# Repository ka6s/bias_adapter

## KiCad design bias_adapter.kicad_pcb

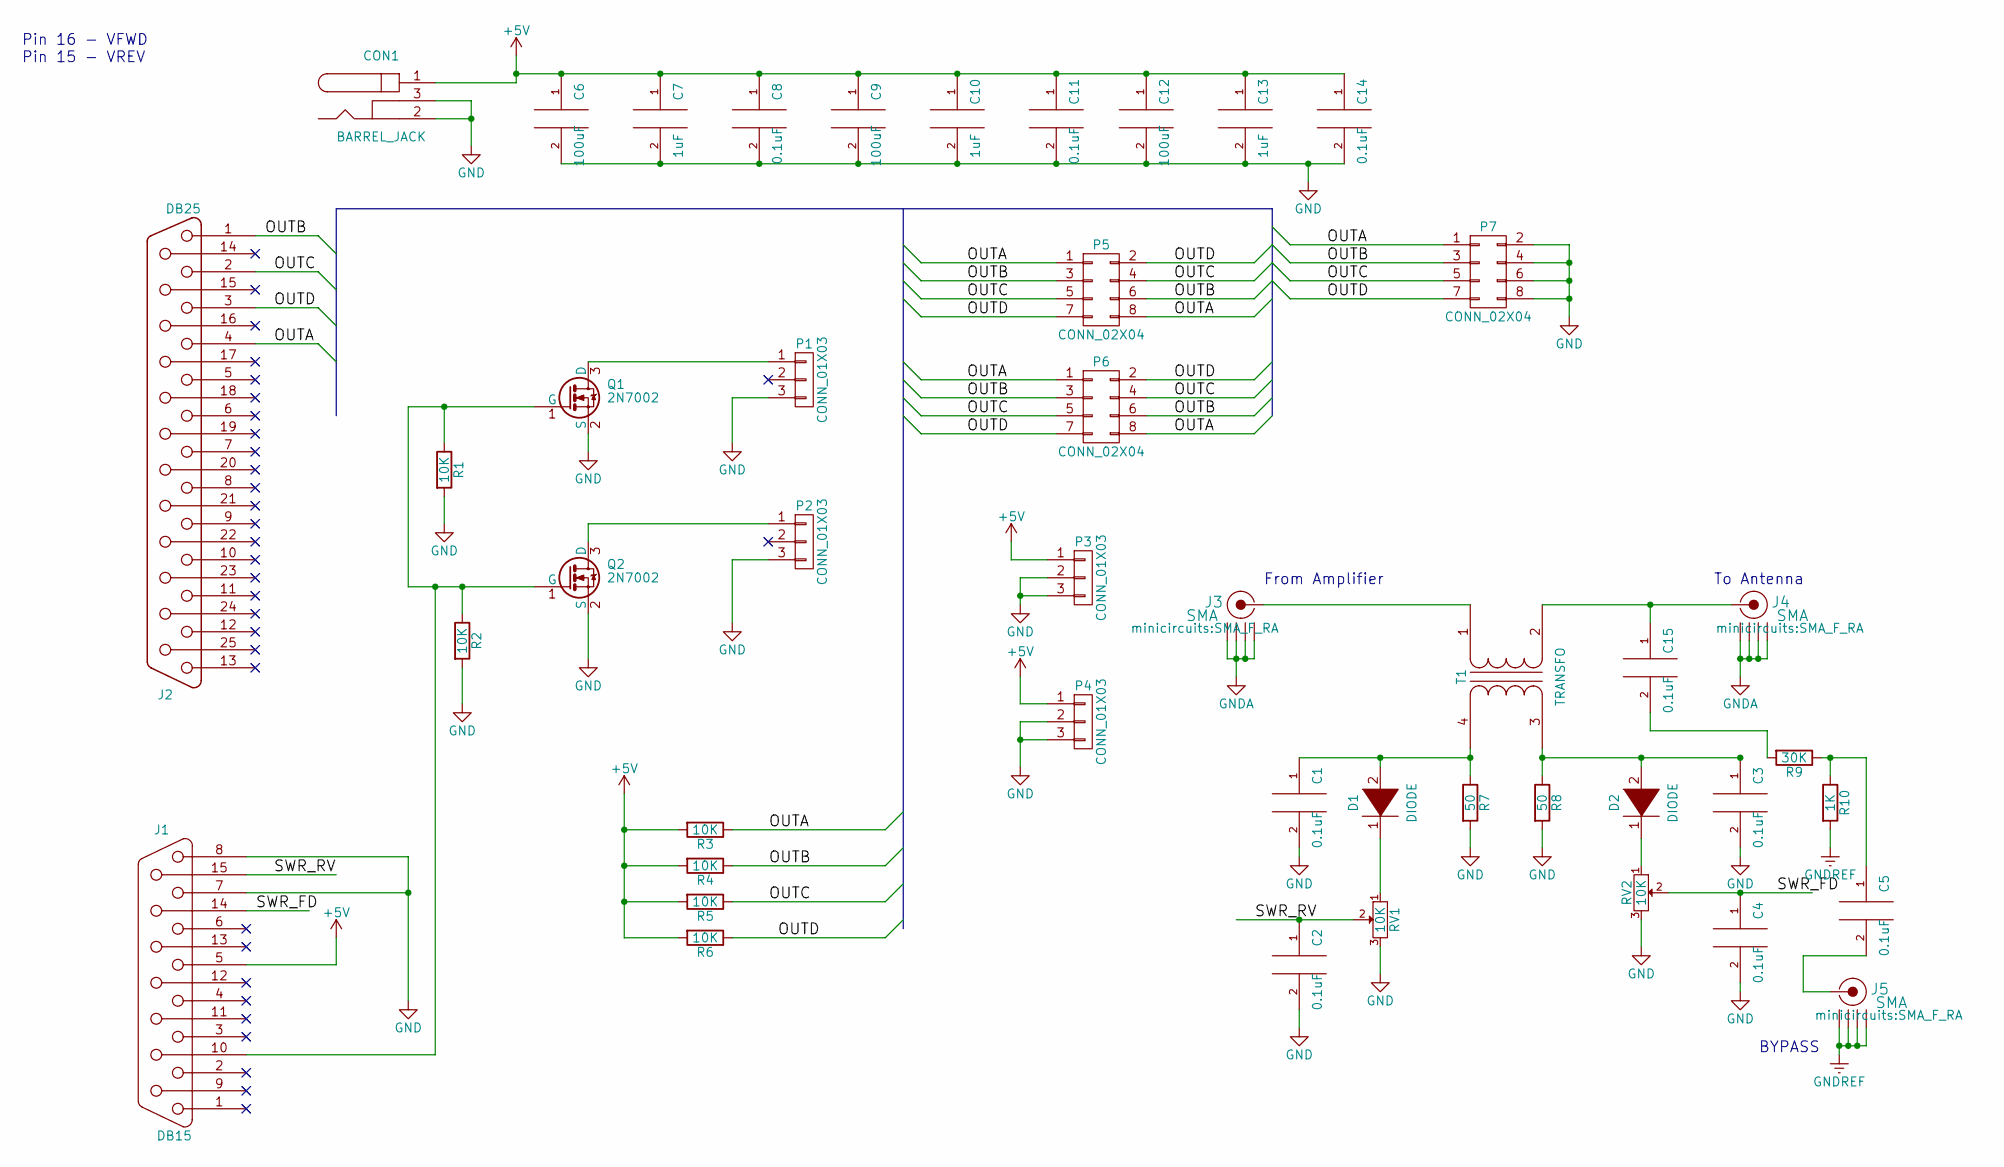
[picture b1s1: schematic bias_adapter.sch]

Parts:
C1, C2, C3, C4, C5, C8, C11, C15: 0.1uF; C_1206_HandSoldering
C6, C9, C12: 100uF; C_1210_HandSoldering
C7, C10, C13: 1uF; C_1210_HandSoldering
C14: 0.1uF; C_1206
CON1: BARREL_JACK
D1, D2: DIODE; Diode_DO-35_SOD27_Horizontal_RM10
J1: DB15; DB15FD
J2: DB25; DB25FD
J3, J4, J5: SMA; SMA_F_RA
P1, P2, P3, P4: CONN_01X03; Pin_Header_Straight_1x03
P5, P6, P7: CONN_02X04; Pin_Header_Straight_2x04
Q1, Q2: 2N7002; SOT-23
R1, R2, R3, R4, R5, R6: 10K; R_1206_HandSoldering
R7, R8: 50; Resistor_Horizontal_RM7mm
R9: 30K; Resistor_Horizontal_RM7mm
R10: 1K; Resistor_Horizontal_RM7mm
RV1, RV2: 10K; Potentiometer_Bourns_3296P_3-8Zoll_Angular_ScrewFront
T1: TRANSFO; NetTie-III

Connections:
+5V: C6.1, C7.1, C8.1, C9.1, C10.1, C11.1, C12.1, C13.1, C14.1, CON1.1, J1.5, P3.1, P4.1, R3.2, R4.2, R5.2, R6.2
/OUTA: J2.4, P5.1, P5.8, P6.1, P6.8, P7.1, R3.1
/OUTB: J2.1, P5.3, P5.6, P6.3, P6.6, P7.3, R4.1
/OUTC: J2.2, P5.4, P5.5, P6.4, P6.5, P7.5, R5.1
/OUTD: J2.3, P5.2, P5.7, P6.2, P6.7, P7.7, R6.1
/SWR_FD: C4.1, J1.14, RV2.2
/SWR_RV: C2.1, J1.15, RV1.2
GND: C1.2, C2.2, C3.2, C4.2, C6.2, C7.2, C8.2, C9.2, C10.2, C11.2, C12.2, C13.2, C14.2, CON1.2, CON1.3, J1.7, J1.8, P1.3, P2.3, P3.2, P3.3, P4.2, P4.3, P7.2, P7.4, P7.6, P7.8, Q1.2 (S), Q2.2 (S), R1.2, R2.2, R7.2, R8.2, RV1.3, RV2.3
GNDA: J3.2 (GND1), J3.3 (GND2), J3.4 (GND3), J3.5 (GND4), J4.2 (GND1), J4.3 (GND2), J4.4 (GND3), J4.5 (GND4)
GNDREF: J5.2 (GND1), J5.3 (GND2), J5.4 (GND3), J5.5 (GND4), R10.2
unnamed: C1.1, D1.2 (A), R7.1, T1.4 (SB)
unnamed: C3.1, D2.2 (A), R8.1, T1.3 (SA)
unnamed: C5.1, R9.1, R10.1
unnamed: C5.2, J5.1 (RF)
unnamed: C15.1, J4.1 (RF), T1.2 (AB)
unnamed: C15.2, R9.2
unnamed: D1.1 (K), RV1.1
unnamed: D2.1 (K), RV2.1
unnamed: J1.10, Q1.1 (G), Q2.1 (G), R1.1, R2.1
unnamed: J3.1 (RF), T1.1 (AA)
unnamed: P1.1, Q1.3 (D)
unnamed: P2.1, Q2.3 (D)

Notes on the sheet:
Pin 16 - VFWD Pin 15 - VREV
BYPASS
From Amplifier
To Antenna

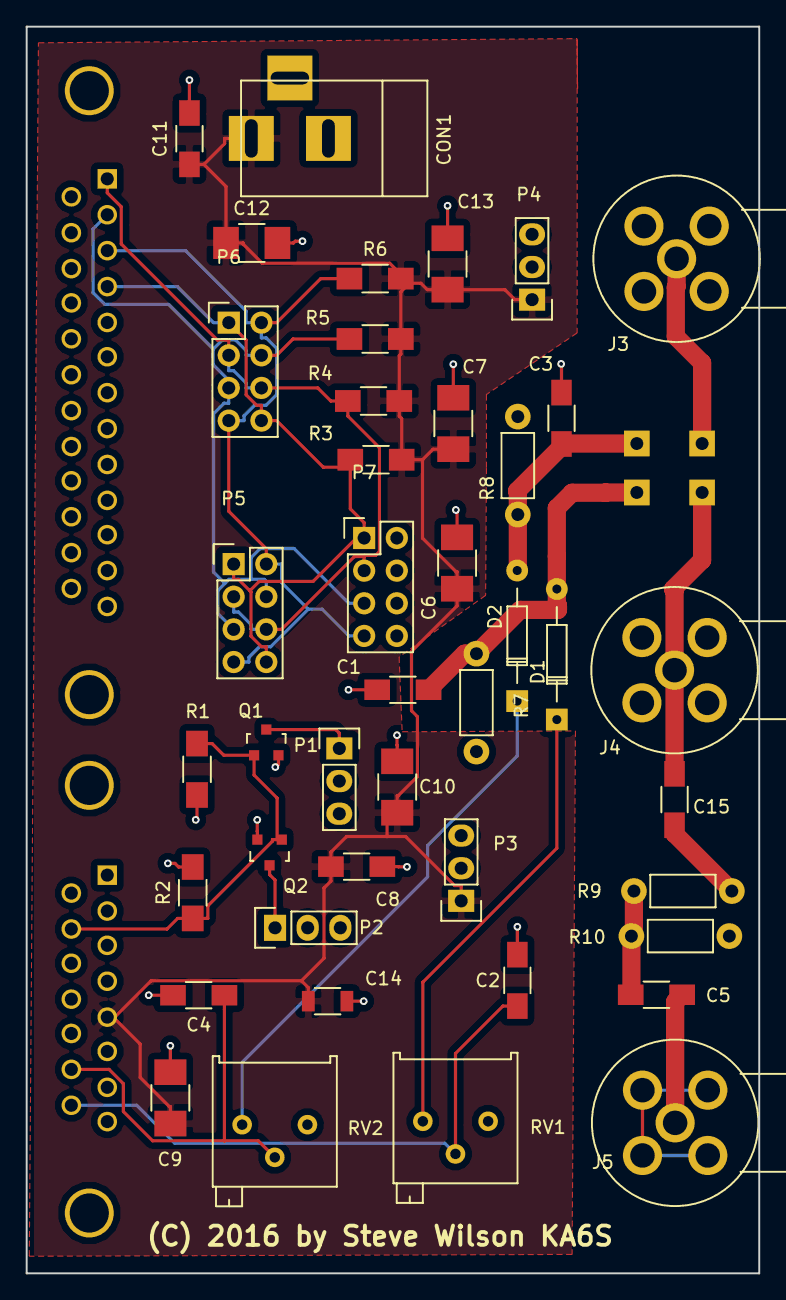
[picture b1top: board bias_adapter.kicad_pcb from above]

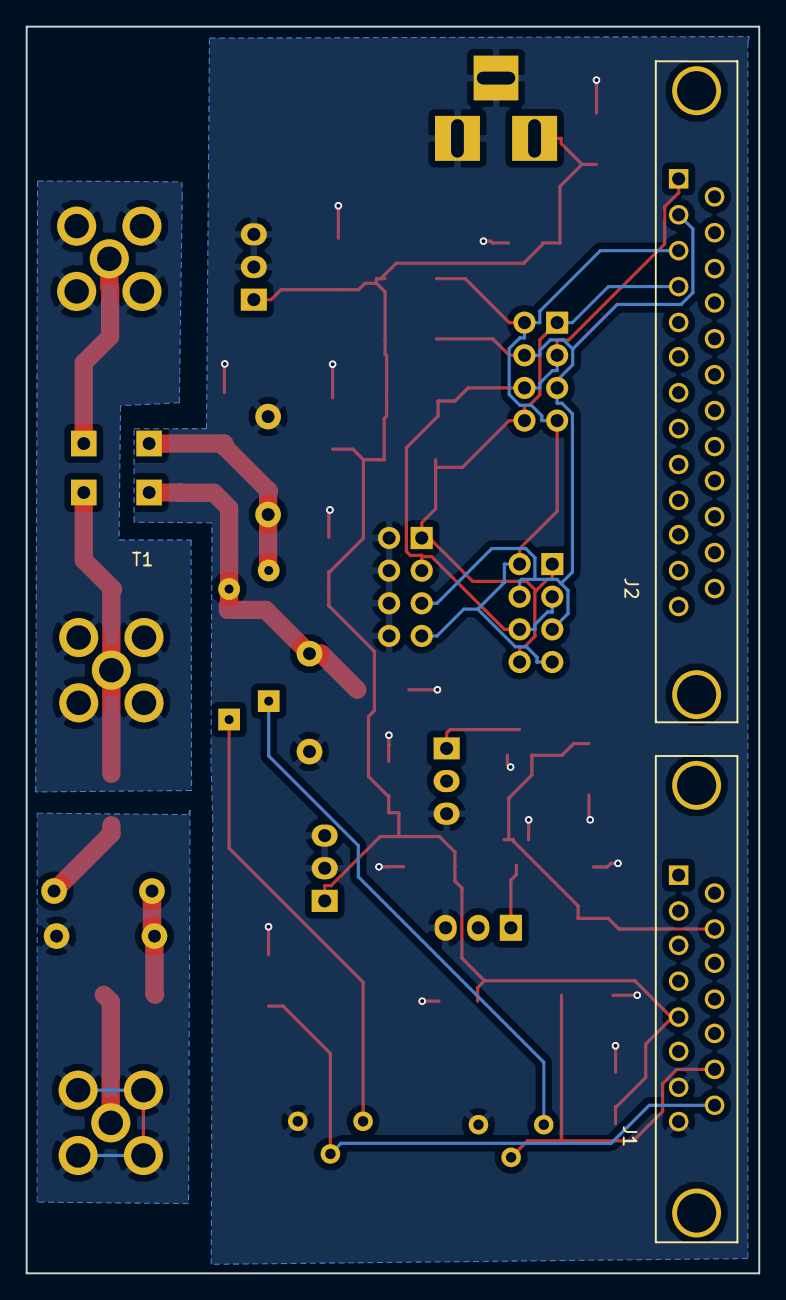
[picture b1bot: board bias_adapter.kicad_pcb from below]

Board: 2 copper layers, 57.0 x 97.0 mm, 45 parts (3 on the bottom side), 22 nets.

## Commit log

2016-11-23 Added

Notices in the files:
bias_adapter.kicad_pcb:
(C) 2016 by Steve Wilson KA6S
